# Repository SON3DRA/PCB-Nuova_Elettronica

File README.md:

# Nuova_Elettronica

i pcb che ho riprodotto, usando Kicad

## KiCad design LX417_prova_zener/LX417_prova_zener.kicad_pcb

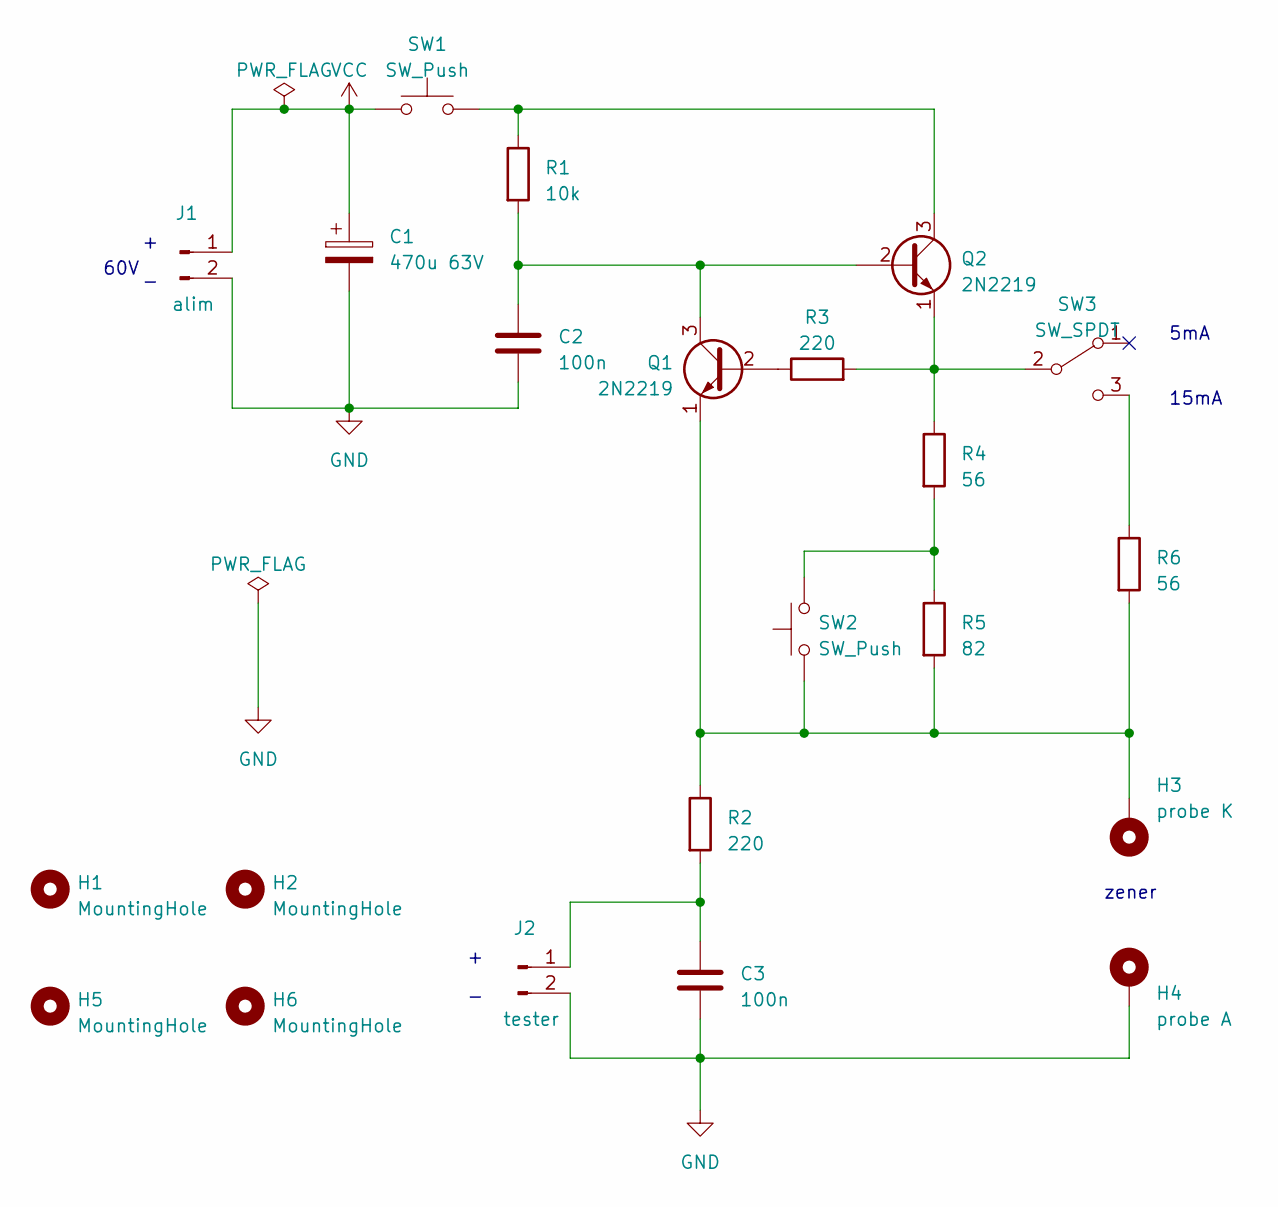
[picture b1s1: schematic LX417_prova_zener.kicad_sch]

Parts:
C1: 470u 63V; CP_Radial_D10.0mm_P5.00mm
C2, C3: 100n; C_Disc_D5.0mm_W2.5mm_P5.00mm
H1, H2, H5, H6: MountingHole; MountingHole_2.2mm_M2
H3: probe K; MountingHole_2.2mm_M2_DIN965_Pad
H4: probe A; MountingHole_2.2mm_M2_DIN965_Pad
J1: alim; PinHeader_1x02_P2.54mm_Vertical
J2: tester; PinHeader_1x02_P2.54mm_Vertical
Q1, Q2: 2N2219; TO-39-3
R1: 10k; R_Axial_DIN0204_L3.6mm_D1.6mm_P7.62mm_Horizontal
R2, R3: 220; R_Axial_DIN0204_L3.6mm_D1.6mm_P7.62mm_Horizontal
R4, R6: 56; R_Axial_DIN0204_L3.6mm_D1.6mm_P7.62mm_Horizontal
R5: 82; R_Axial_DIN0204_L3.6mm_D1.6mm_P7.62mm_Horizontal
SW1, SW2: SW_Push; PinHeader_1x02_P2.54mm_Vertical
SW3: SW_SPDT; PinHeader_1x03_P2.54mm_Vertical

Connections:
GND: C1.2, C2.2, C3.2, H4.1, J1.2, J2.2
unnamed: C3.1, J2.1, R2.2
unnamed: Q1.2 (B), R3.1
unnamed: C2.1, Q1.3 (C), Q2.2 (B), R1.2
unnamed: H3.1, Q1.1 (E), R2.1, R5.2, R6.2, SW2.1
unnamed: Q2.3 (C), R1.1, SW1.2
unnamed: Q2.1 (E), R3.2, R4.1, SW3.2 (B)
unnamed: R4.2, R5.1, SW2.2
unnamed: R6.1, SW3.3 (C)
VCC: C1.1, J1.1, SW1.1

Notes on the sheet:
5mA
zener
15mA
60V

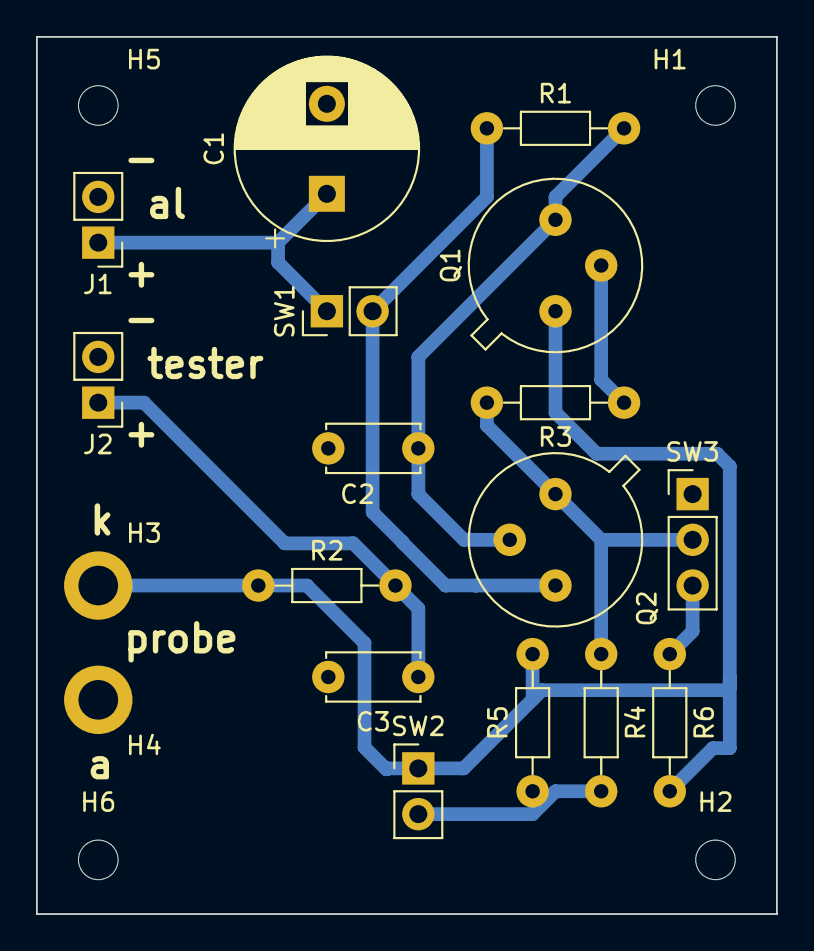
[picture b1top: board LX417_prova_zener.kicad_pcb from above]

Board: 2 copper layers, 41.1 x 48.7 mm, 22 parts (0 on the bottom side), 10 nets.

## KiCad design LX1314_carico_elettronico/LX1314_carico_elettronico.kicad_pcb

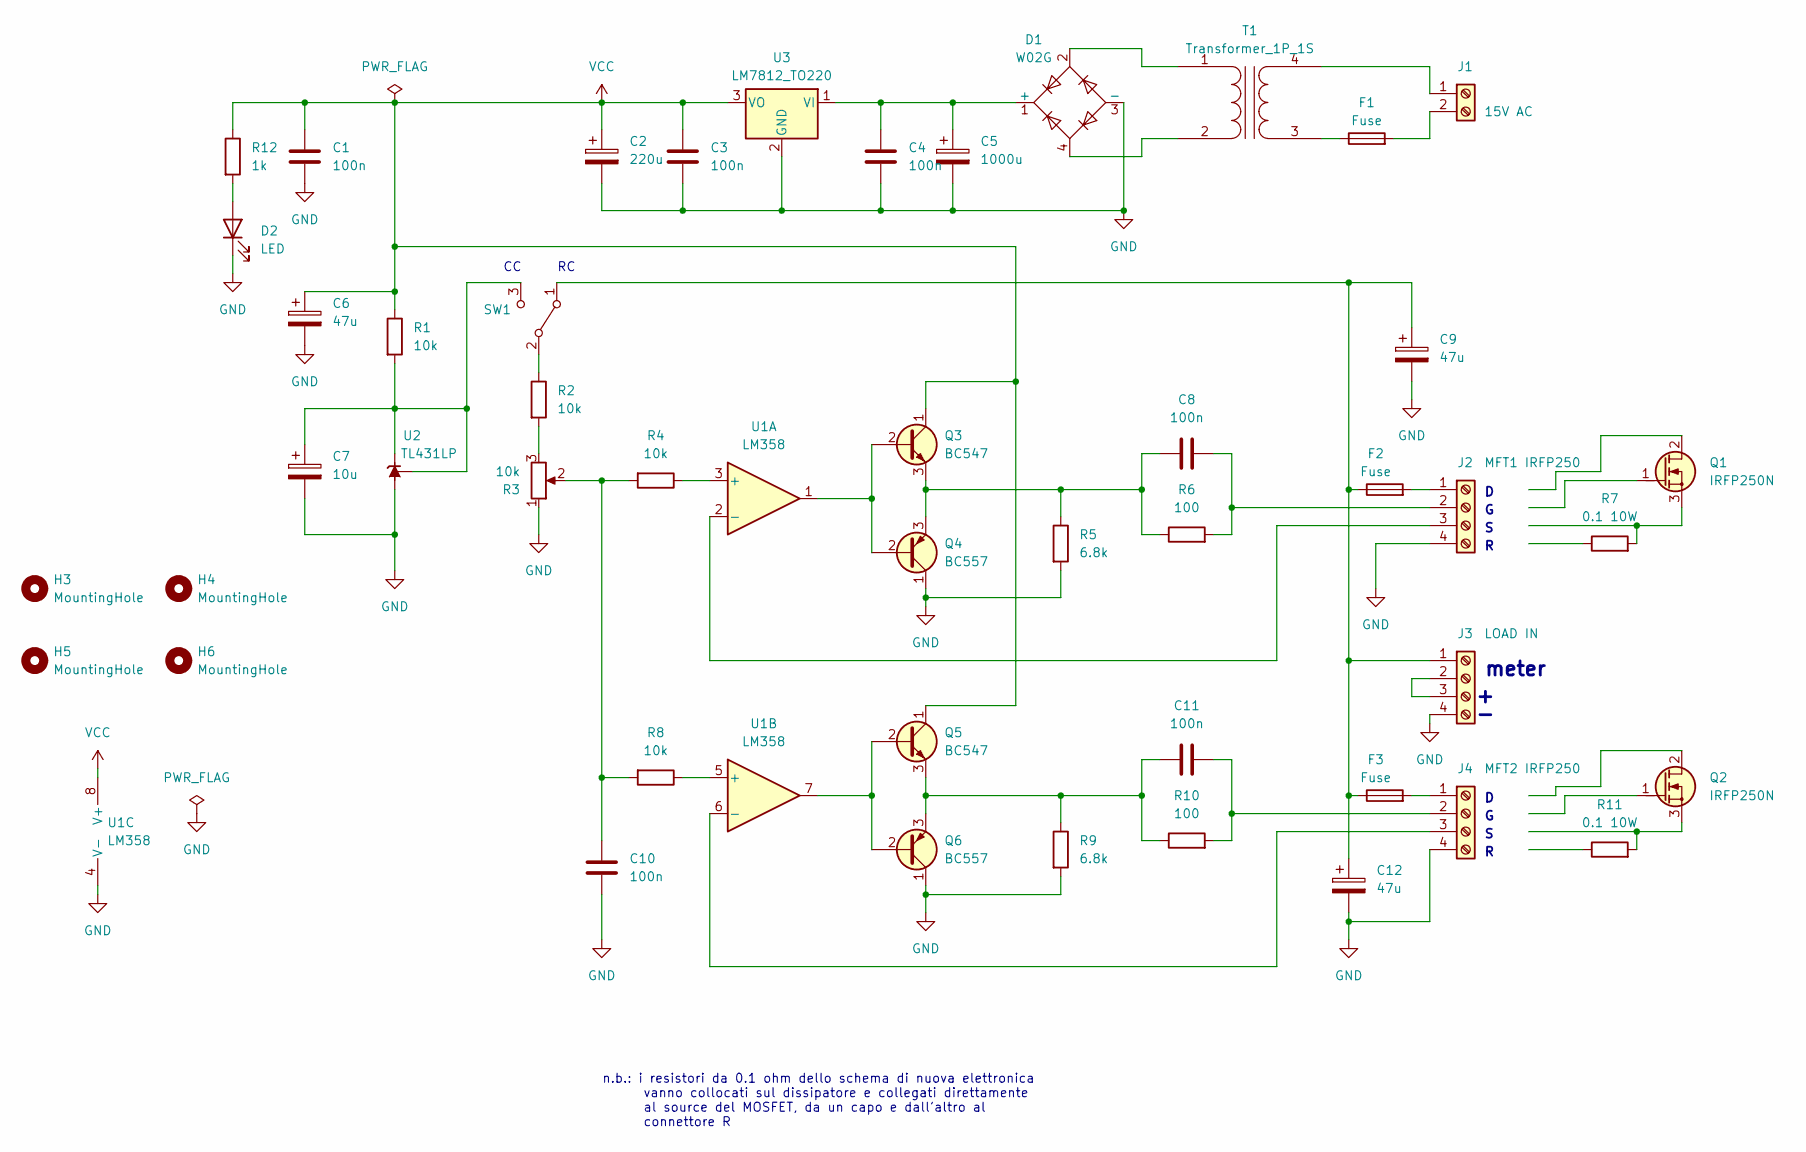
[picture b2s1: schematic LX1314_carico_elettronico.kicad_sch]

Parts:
C1, C3, C4, C8, C10, C11: 100n; C_Disc_D5.0mm_W2.5mm_P5.00mm
C2: 220u; CP_Radial_D8.0mm_P5.00mm
C5: 1000u; CP_Radial_D10.0mm_P7.50mm
C6, C9, C12: 47u; CP_Radial_D8.0mm_P5.00mm
C7: 10u; CP_Radial_D8.0mm_P5.00mm
D1: W02G; Diode_Bridge_Round_D9.0mm
D2: LED; LED_D5.0mm_Clear
F1: Fuse; Fuseholder_Clip-5x20mm_Keystone_3518P_Inline_P23.11x6.76mm_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
F2, F3: Fuse; Fuseholder_Keystone_3555-2
H3, H4, H5, H6: MountingHole; MountingHole_3.2mm_M3
J1: 15V AC; Altech_AK300_1x02_P5.00mm_45-Degree
J2: MFT1 IRFP250; Altech_AK300_1x04_P5.00mm_45-Degree
J3: LOAD IN; Altech_AK300_1x04_P5.00mm_45-Degree
J4: MFT2 IRFP250; Altech_AK300_1x04_P5.00mm_45-Degree
Q1, Q2: IRFP250N; TO-247-3_Vertical_GDS
Q3, Q5: BC547; TO-92_Inline_Wide_CBE
Q4, Q6: BC557; TO-92_Inline_Wide_CBE
R1, R2, R4, R8: 10k; R_Axial_DIN0204_L3.6mm_D1.6mm_P7.62mm_Horizontal
R3: 10k; Potentiometer_ACP_CA9-H5_Horizontal
R5, R9: 6.8k; R_Axial_DIN0204_L3.6mm_D1.6mm_P7.62mm_Horizontal
R6, R10: 100; R_Axial_DIN0204_L3.6mm_D1.6mm_P7.62mm_Horizontal
R7, R11: 0.1 10W
R12: 1k; R_Axial_DIN0204_L3.6mm_D1.6mm_P7.62mm_Horizontal
SW1: Altech_AK300_1x03_P5.00mm_45-Degree
T1: Transformer_1P_1S; Transformer_CHK_EI48-8VA_1xSec
U1: LM358; DIP-8_W7.62mm_LongPads
U2: TL431LP; TO-92_Inline_Wide_CBE
U3: LM7812_TO220; TO-220-3_Vertical

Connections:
GND: C1.2, C2.2, C3.2, C4.2, C5.2, C6.2, C7.2, C9.2, C10.2, C12.2, D1.3 (-), D2.1 (K), J2.4, J3.4, J4.4, Q4.1 (C), Q6.1 (C), R3.1, R5.2, R9.2, U1.4 (V-), U2.2 (A), U3.2 (GND)
unnamed: C10.1, R3.2, R4.2, R8.2
unnamed: C4.1, C5.1, D1.1 (+), U3.1 (VI)
unnamed: D2.2 (A), R12.2
unnamed: J1.1, T1.4 (SB)
unnamed: F1.2, J1.2
unnamed: F2.2, J2.1
unnamed: C8.2, J2.2, R6.2
unnamed: J2.3, U1.2 (-)
unnamed: C9.1, C12.1, F2.1, F3.1, J3.1, SW1.1 (A)
unnamed: J3.2, J3.3
unnamed: F3.2, J4.1
unnamed: C11.2, J4.2, R10.2
unnamed: J4.3, U1.6 (-)
unnamed: Q1.3 (S), R7.2
unnamed: Q2.3 (S), R11.2
unnamed: Q3.2 (B), Q4.2 (B), U1.1
unnamed: C8.1, Q3.3 (E), Q4.3 (E), R5.1, R6.1
unnamed: Q5.2 (B), Q6.2 (B), U1.7
unnamed: C11.1, Q5.3 (E), Q6.3 (E), R9.1, R10.1
unnamed: R2.2, R3.3
unnamed: R2.1, SW1.2 (B)
unnamed: C7.1, R1.2, SW1.3 (C), U2.1 (REF), U2.3 (K)
unnamed: D1.2, T1.1 (AA)
unnamed: D1.4, T1.2 (AB)
unnamed: F1.1, T1.3 (SA)
unnamed: R4.1, U1.3 (+)
unnamed: R8.1, U1.5 (+)
VCC: C1.1, C2.1, C3.1, C6.1, Q3.1 (C), Q5.1 (C), R1.1, R12.1, U1.8 (V+), U3.3 (VO)

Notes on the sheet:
n.b.: i resistori da 0.1 ohm dello schema di nuova elettronica vanno collocati sul dissipatore e collegati direttamente al source del MOSFET, da un capo e dall'altro al connettore R
meter

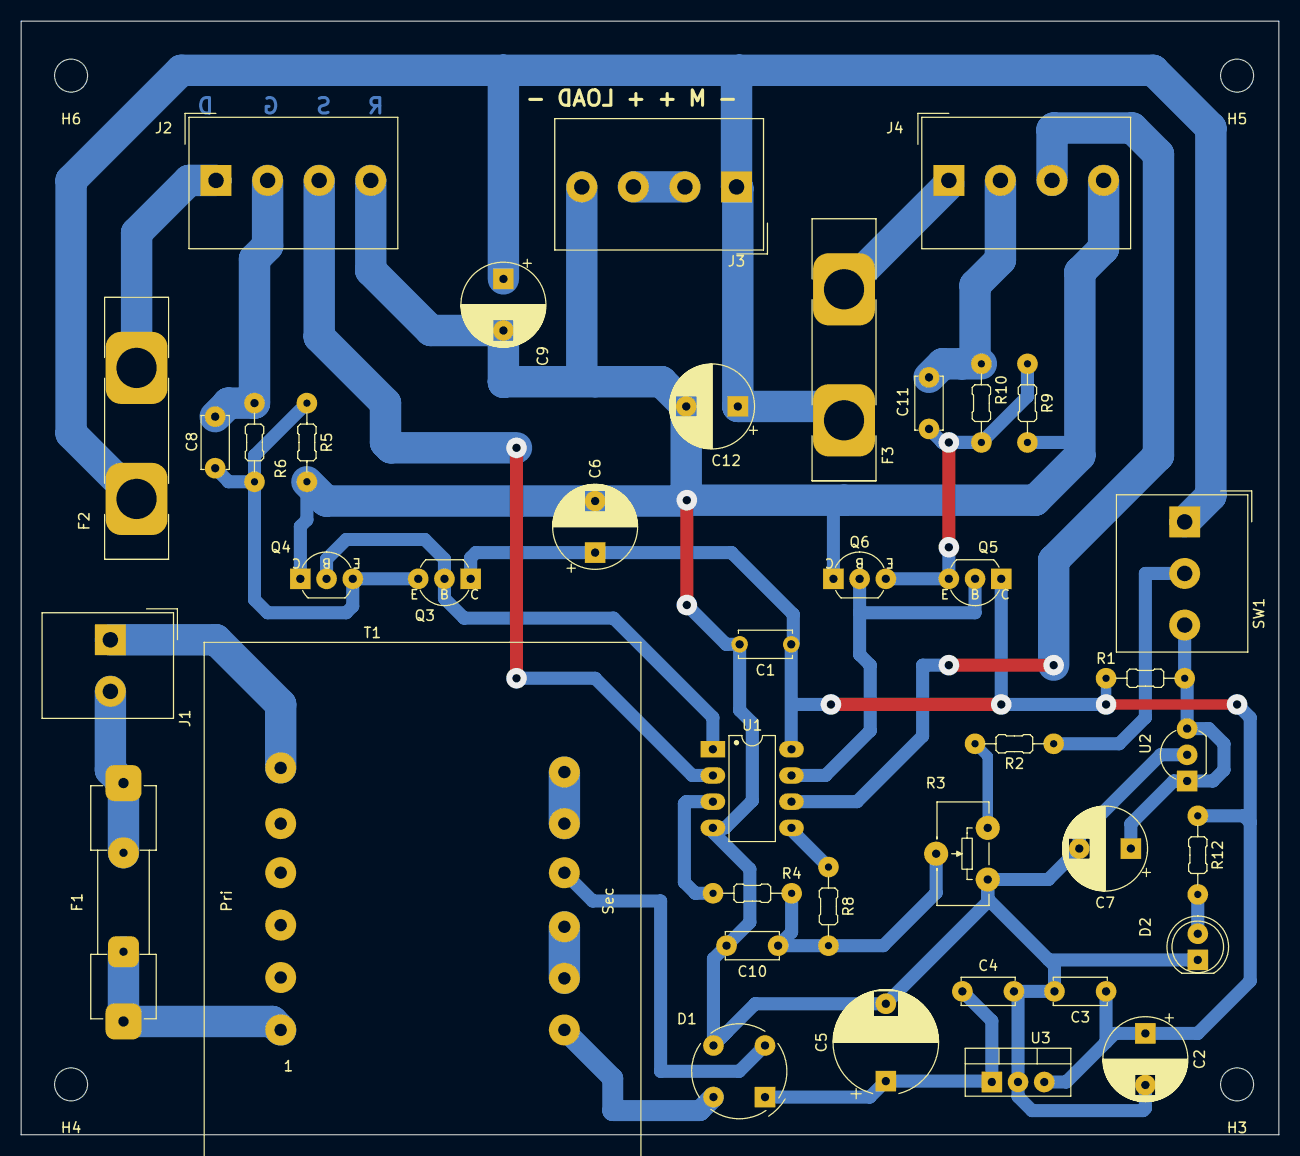
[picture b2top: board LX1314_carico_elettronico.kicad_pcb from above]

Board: 2 copper layers, 121.9 x 107.9 mm, 44 parts (0 on the bottom side), 27 nets.

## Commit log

2024-11-19 Add files via upload
    LX1476 Oscillofono per lo studio della telegrafia
